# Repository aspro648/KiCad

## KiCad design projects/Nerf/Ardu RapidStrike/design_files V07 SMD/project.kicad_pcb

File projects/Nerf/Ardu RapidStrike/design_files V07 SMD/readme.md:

ArduStrike

Pusher Fuse 1206: 1A https://www.digikey.com/short/p532qq
Main: 1812: 3.5A https://www.digikey.com/short/p532pr

TODO:

ISP to back
second MOSFET?

Main Board
----------------
- 1 ea., IC MCU 8BIT 32KB FLASH 32TQFP, ATMEGA328P-AUR, https://www.digikey.com/short/prrf1p
- 1 ea., Y1 CER RES 16.0000MHZ 15PF SMD, CSTNE16M0V530000R0, https://www.digikey.com/short/p55m1p
- 1 ea., IC REG LINEAR 5V 250MA SOT89-3, Microchip MCP1702-5002E/TO, https://www.digikey.com/short/p5cbrh
- 1 ea., MOSFET N-CH 30V 58A DPAK, Infineon IRLR8729, https://www.digikey.com/short/pm0rdq3
- 1 ea., TC78H611FNG IC MOTOR DRIVER 16TSSOP, https://www.digikey.com/short/p5559f
- 1 ea., PTC RESET FUSE 16V Ih=1.25A It=2.5A  1812, https://www.digikey.com/short/p555q2
- 1 ea., PTC RESET FUSE 16V Ih=500MA It=1A 1210, https://www.digikey.com/short/p532qq
- 1 ea., F1 PTC 1206, Bel 0ZCJ0025AF2E, https://www.digikey.com/short/jfcbc8
- 1 ea., DIODE GEN PURP 50V 1A SMB, https://www.digikey.com/short/p555z5
- 3 ea., Hall Effect Sensor, Diodes Incorporated AH9246-P-B, https://www.digikey.com/short/p5cb4f
- 1 ea., 0.96 Inch 128x64 I2C OLED, https://www.amazon.com/gp/product/B072Q2X2LL/
- 1 ea., CONN HEADER R/A 6POS 2.54MM,  https://www.digikey.com/short/p55hf2

- 7 ea., CAP CER 0.1UF 16V X7R 0805, https://www.digikey.com/short/p5r2hm
- 2 ea., CAP CER 1UF 16V X7R 0805, https://www.digikey.com/short/p5r25m
- 1 ea., CAP CER 10UF 16V X5R 0805, https://www.digikey.com/short/p5r2cv

- 1 ea., RES SMD 100 OHM 5% 1/8W 0805, https://www.digikey.com/short/p55997
- 5 ea., RES SMD 1K OHM 5% 1/8W 0805, https://www.digikey.com/short/p559mn
- 11 ea., RES 10K OHM 1% 1/4W 0805, https://www.digikey.com/short/p55980

- 1 ea., AUDIO PIEZO TRANSDUCER 30V TH, https://www.digikey.com/short/p5r22q

- 1 ea., CONN HEADER R/A 2POS 1.25MM, https://www.digikey.com/short/p5r2dn
- 1 ea., 2POS PicoBlade housing, https://www.digikey.com/short/p4wz0d

- 1 ea., CONN HEADER SMD R/A 3POS https://www.digikey.com/short/p5r208
- 1 ea., 3POS PicoBlade housing, https://www.digikey.com/short/pmwzf2

- 1 ea., CONN HEADER R/A 4POS 1.25MM, https://www.digikey.com/short/p5r2nj
- 1 ea., 4POS PicoBlade housing, https://www.digikey.com/short/p4wzd1

- 1 ea., CONN HEADER SMD R/A 10POS 1.25MM, https://www.digikey.com/short/p5r2vz
- 1 ea., CONN HOUSING 10POS 1.25MM NATURAL, https://www.digikey.com/short/p5rhr3

12" PRE-CRIMP 1853 RED, https://www.digikey.com/short/p4wzvf
12" PRE-CRIMP 1853 BLACK, https://www.digikey.com/short/p4wz1p
12" PRE-CRIMP 1853 BLUE, https://www.digikey.com/short/p4wz14
12" PRE-CRIMP 1853 ORANGE, https://www.digikey.com/short/p4wz1r
12" PRE-CRIMP 1853 GREEN, https://www.digikey.com/short/p4w4c4

10" PRE-CRIMP 1852 RED, https://www.digikey.com/short/p937zh
10" PRE-CRIMP 1852 BLACK, https://www.digikey.com/short/p937zv
10" PRE-CRIMP 1852 YELLOW, https://www.digikey.com/short/p9374t
10" PRE-CRIMP 1852 GREEN, https://www.digikey.com/short/p9374z
10" PRE-CRIMP 1852 ORANGE, https://www.digikey.com/short/p9374f
10" PRE-CRIMP 1852 BLUE, https://www.digikey.com/short/p937mc

16 AWG Silicone wire, https://www.amazon.com/BNTECHGO-Silicone-Flexible-Strands-Stranded/dp/B00TG1TRL2
18 AWG Silicone wire (7.5A, $0.40/ft), https://www.amazon.com/Silicone-Electrical-Conductor-Parallel-Flexible/dp/B07FMRDP87
16 AWG Silicone wire (12A, $0.70/ft), https://www.amazon.com/Silicone-Electrical-Conductor-Parallel-Flexible/dp/B07FMLVF84

XT60 connector male

Optional:
FTDI SERIAL TTL-232 USB CABLE, https://www.digikey.com/short/p4w47d
SPARKFUN FT231X BREAKOUT, https://www.digikey.com/short/p4w4qb
- 1 ea., 3mm IR LED, https://www.digikey.com/short/pmwzdq
- 1 ea., NPN photo transistor, https://www.digikey.com/short/pmwzdb

Motor Spec Sheet:
----------------
https://docs.google.com/spreadsheets/d/12gOU-GbuqdGVzpOjZJvQ_gq1Nmw63c_sd13Wt4bfn1E/edit#gid=0

Revisions
----------------
0.1 Added push button to A0.
0.3 Removed XT30 connectors, added PTC, fuse holder.
0.4 Major component repositioning
0.5 Trigger moved clip connector
	Pusher Bat conn to 5.08mm.
	Mosfet layout change
0.6 SMD Layout
0.7 Picoblade, piezo, FTDI to through-hole. 10K resistor divider.

License
----------------
[Attribution-ShareAlike 3.0 United States (CC BY-SA 3.0 US)](https://creativecommons.org/licenses/by-sa/3.0/us/)

You are free to:

- Share — copy and redistribute the material in any medium or format
- Adapt — remix, transform, and build upon the material

Under the following terms:

- Attribution — You must give appropriate credit, provide a link to the license, and indicate if changes were made. You may do so in any reasonable manner, but not in any way that suggests the licensor endorses you or your use.
- ShareAlike — If you remix, transform, or build upon the material, you must distribute your contributions under the same license as the original.

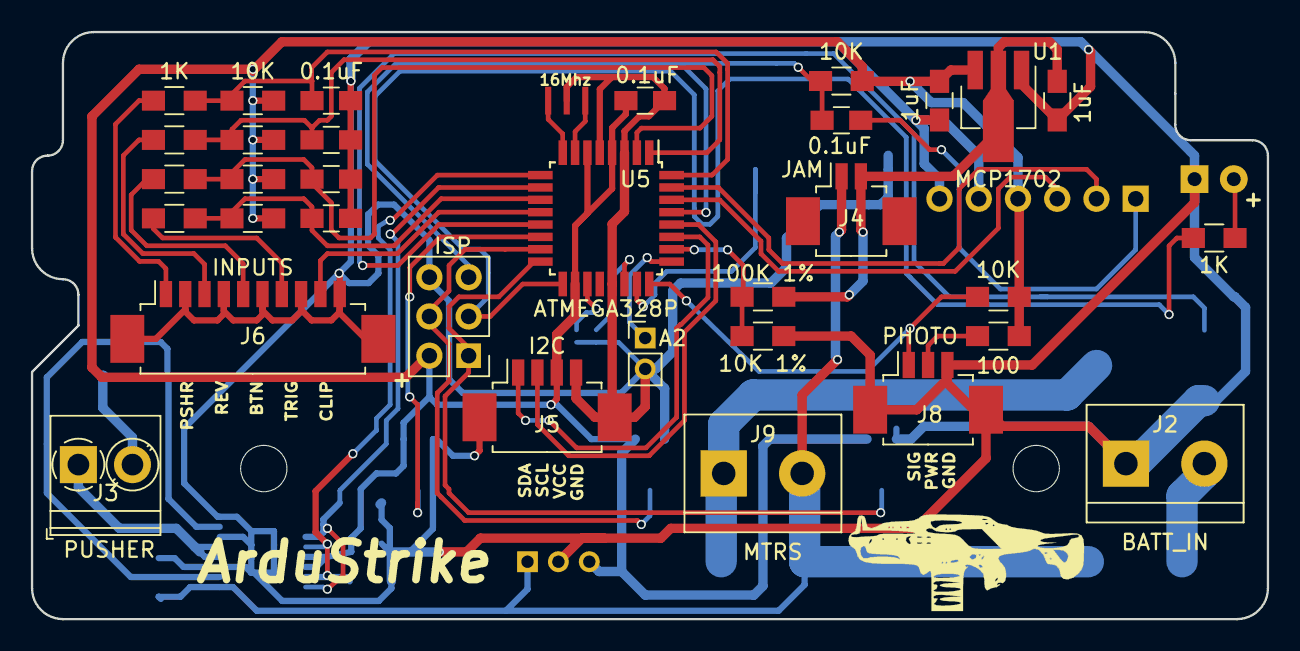
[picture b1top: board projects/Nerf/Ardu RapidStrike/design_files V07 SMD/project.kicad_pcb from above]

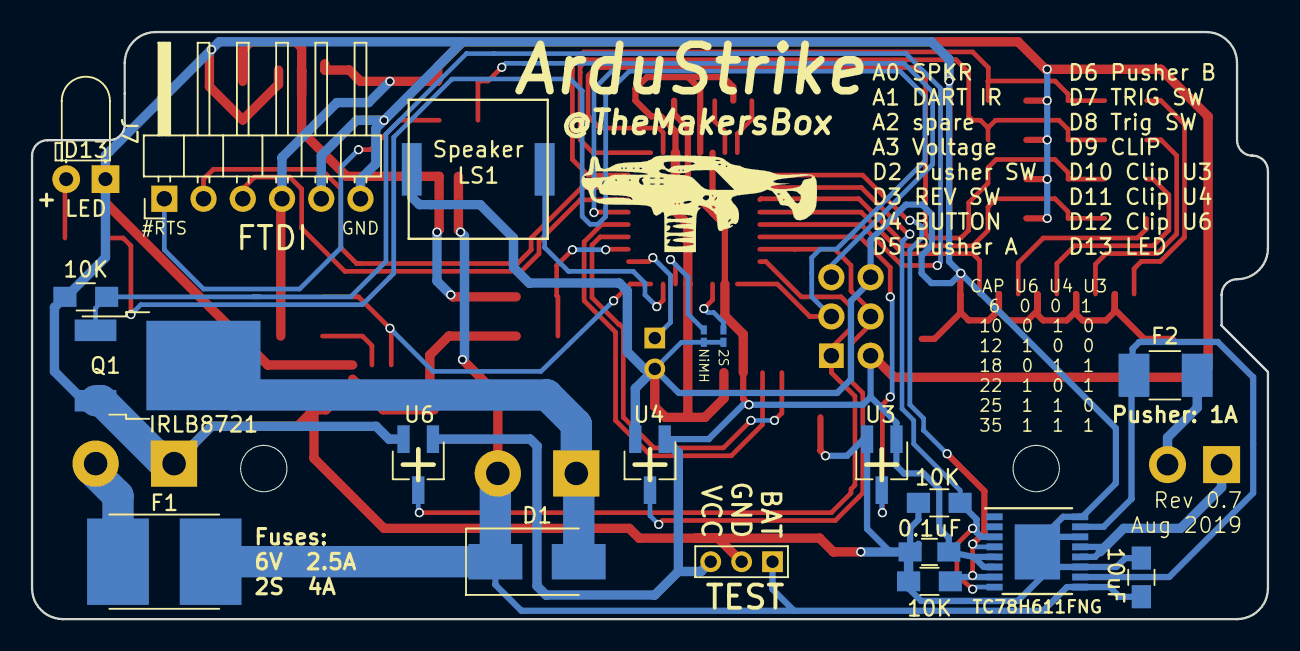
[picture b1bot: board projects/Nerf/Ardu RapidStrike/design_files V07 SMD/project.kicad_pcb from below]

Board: 2 copper layers, 80.0 x 38.0 mm, 55 parts (19 on the bottom side), 41 nets.

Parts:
C1, C4: 1uF; C_0805_HandSoldering
C2: 10uF; C_0805_HandSoldering
C3, C5, C6, C7, C8, C9, C10: 0.1uF; C_0805_HandSoldering
CON1: ISP; Pin_Header_Straight_2x03_Pitch2.54mm
D1: KICKBACK; D_SMB_Handsoldering
D13: LED; LED_D3.0mm_Horizontal_O1.27mm_Z10.0mm
F1: PTC; Fuse_SMD2920
F2: PTC; Fuse_SMD1210
J1: TEST; Pin_Header_Straight_1x03_Pitch2.00mm
J2: BATT_IN; TerminalBlock_bornier-2_P5.08mm
J3: PUSHER; TerminalBlock_Phoenix_PT-1,5-2-3.5-H_1x02_P3.50mm_Horizontal
J4: JAM; Molex_PicoBlade_53261-0271_02x1.25mm_Angled
J5: I2C; Molex_PicoBlade_53261-0471_04x1.25mm_Angled
J6: INPUTS; Molex_PicoBlade_53261-1071_10x1.25mm_Angled
J7: FTDI; Pin_Header_Angled_1x06_Pitch2.54mm
J8: PHOTO; Molex_PicoBlade_53261-0371_03x1.25mm_Angled
J9: MTRS; TerminalBlock_bornier-2_P5.08mm
J11: A2; Pin_Header_Straight_1x02_Pitch2.00mm
J14, J14#2: NPTH; SolderWirePad_single_2-5mmDrill
JP1: 2S; JMPR
JP2: NiMH; JMPR
LS1: Speaker; PS1240_piezo
Q1: IRLB8721; TO-252-2_hand_soldering
R1, R3, R4, R6, R9, R10, R17, R19, R20: 10K; R_0805_HandSoldering
R2, R5, R7, R11, R18: 1K; R_0805_HandSoldering
R8: 100K 1%; R_0805_HandSoldering
R12: 10K 1%; R_0805_HandSoldering
R21: 100; R_0805_HandSoldering
U1: MCP1702; SOT-89-3_Handsoldering
U2: TC78H611FNG; TSSOP-16-1EP_4.4x5mm_Pitch0.65mm
U3, U4, U6: HALL SENSOR; SC-59_Handsoldering
U5: ATMEGA328P; TQFP-32_7x7mm_Pitch0.8mm
Y1: 16Mhz; Resonator_SMD_CTSC_1.3mmx3.2mm

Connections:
/0(Rx): J7.3, U5.30
/1(Tx): J7.2, U5.31
/2: C6.1, R4.1, R5.2, U5.32
/3(**): C7.1, R6.1, R7.2, U5.1
/4: C10.1, R18.2, R19.1, U5.2
/5(**): R1.2, U2.4, U2.7, U5.9
/6(**): R3.2, U2.3, U2.8, U5.10
/7: C8.1, R10.1, R11.2, U5.11
/8: J6.9, U5.12
/9(**): Q1.1, R9.2, U5.13
/10(SS): U3.3, U5.14
/11(MOSI): CON1.4, U4.3, U5.15
/12(MISO): CON1.1, U5.16, U6.3
/13(SCK): CON1.3, R2.1, U5.17
/#RTS: C9.1, J7.1
/A0: LS1.1, U5.23
/A1: J8.1, R20.2, U5.24
/A2: J11.1, U5.25
/A3: R8.1, R12.1, U5.26
/A4(SDA): J5.1, U5.27
/A5(SCL): J5.2, U5.28
/BATT: C2.1, D1.1, F1.1, J1.1, J4.1, J9.2, U2.9
/Reset: C9.2, CON1.5, R17.1, U5.29
/Vin: C1.1, J4.2, R8.2, U1.2
GND: C1.2, C2.2, C3.2, C4.2, C5.2, C6.2, C7.2, C8.2, C10.2, CON1.6, D13.1, J1.2, J2.1, J5.4, J6.2, J6.4, J6.6, J6.8, J6.10, J7.5, J7.6, J8.3, J11.2, JP1.1, JP2.1, LS1.2, Q1.3, R1.1, R3.1, R9.1, R12.2, U1.1, U2.11, U2.14, U2.16, U3.2, U4.2, U5.3, U5.5, U5.21, U6.2, Y1.2
unnamed: D1.2, J9.1, Q1.2
unnamed: D13.2, R2.2
unnamed: F1.2, J2.2
unnamed: F2.1, U2.10, U2.15
unnamed: F2.2, J3.2
unnamed: J3.1, U2.12, U2.13
unnamed: J6.1, R5.1
unnamed: J6.3, R7.1
unnamed: J6.5, R18.1
unnamed: J6.7, R11.1
unnamed: J8.2, R21.2
unnamed: JP1.2, U5.19
unnamed: JP2.2, U5.22
unnamed: U5.7, Y1.3
unnamed: U5.8, Y1.1
VCC: C3.1, C4.1, C5.1, CON1.2, J1.3, J5.3, J7.4, R4.2, R6.2, R10.2, R17.2, R19.2, R20.1, R21.1, U1.3, U2.5, U2.6, U3.1, U4.1, U5.4, U5.6, U5.18, U6.1

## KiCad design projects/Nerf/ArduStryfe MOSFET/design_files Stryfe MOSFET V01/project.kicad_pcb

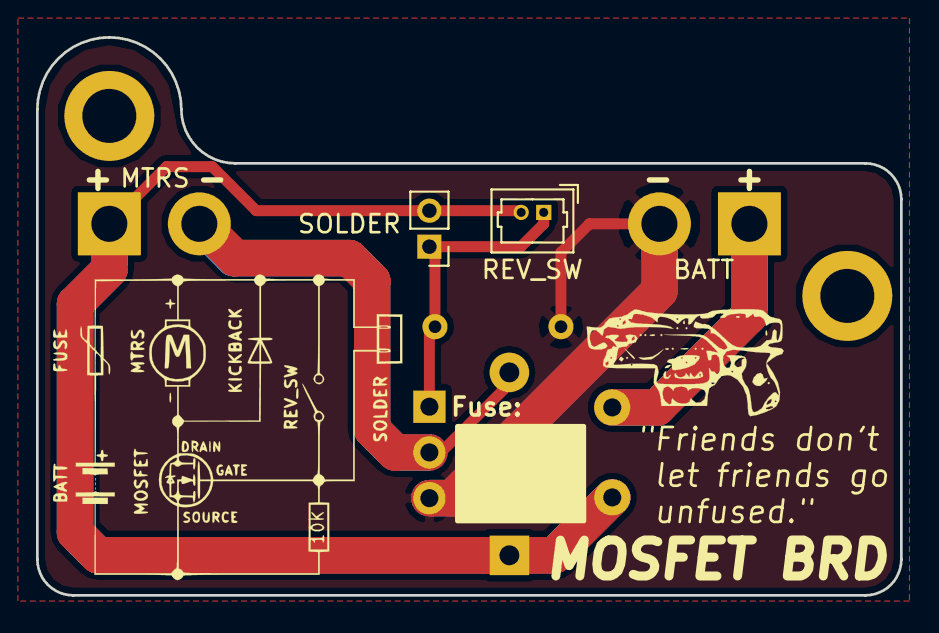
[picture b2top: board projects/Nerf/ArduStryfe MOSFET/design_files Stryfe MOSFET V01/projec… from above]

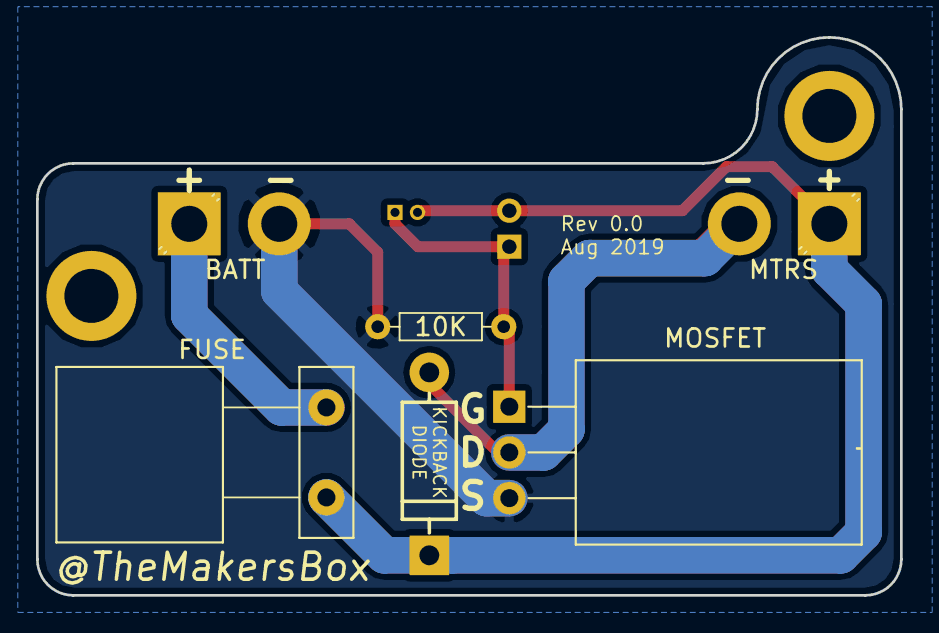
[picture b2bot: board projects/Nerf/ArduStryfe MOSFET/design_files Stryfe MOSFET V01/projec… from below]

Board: 2 copper layers, 48.0 x 31.0 mm, 11 parts (6 on the bottom side), 5 nets.

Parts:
BT1: BATT; Terminal_no_silk
D1: KICKBACK; D_DO-41
F1: FUSE; Fuse_Littelfuse-LVR125
J1: REV_SW; Molex_PicoBlade_53047-0210_02x1.25mm_Straight
J3: SOLDER; Pin_Header_Straight_1x02_Pitch2.00mm
J14, J14#2: MOUNT; SolderWirePad_single_2-5mmDrill
M1: MTRS; Terminal_no_silk
Q1: MOSFET; TO-220-3_Horizontal
R1: 10K; R__P7mm
Ref**: Val**; sch

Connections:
GND: BT1.2, Q1.3, R1.1
unnamed: BT1.1, F1.2
unnamed: D1.1, F1.1, J1.2, J3.2, M1.1
unnamed: D1.2, M1.2, Q1.2
unnamed: J1.1, J3.1, Q1.1, R1.2

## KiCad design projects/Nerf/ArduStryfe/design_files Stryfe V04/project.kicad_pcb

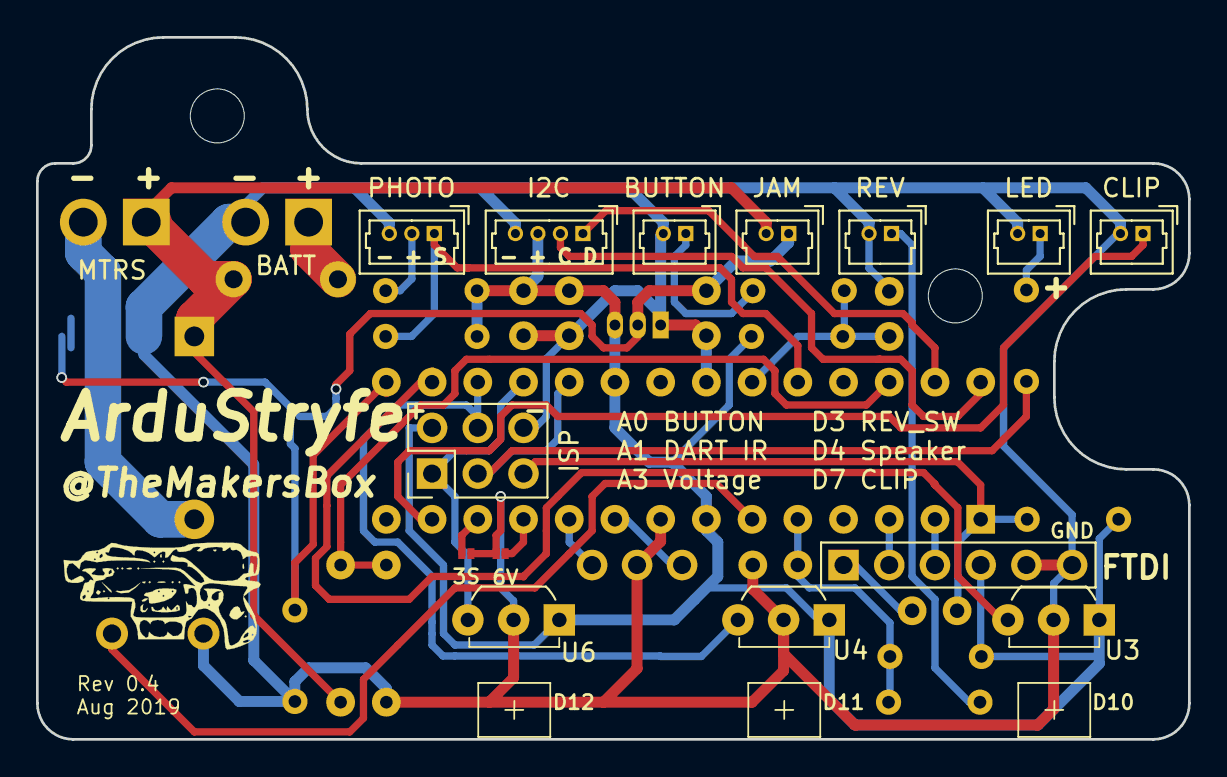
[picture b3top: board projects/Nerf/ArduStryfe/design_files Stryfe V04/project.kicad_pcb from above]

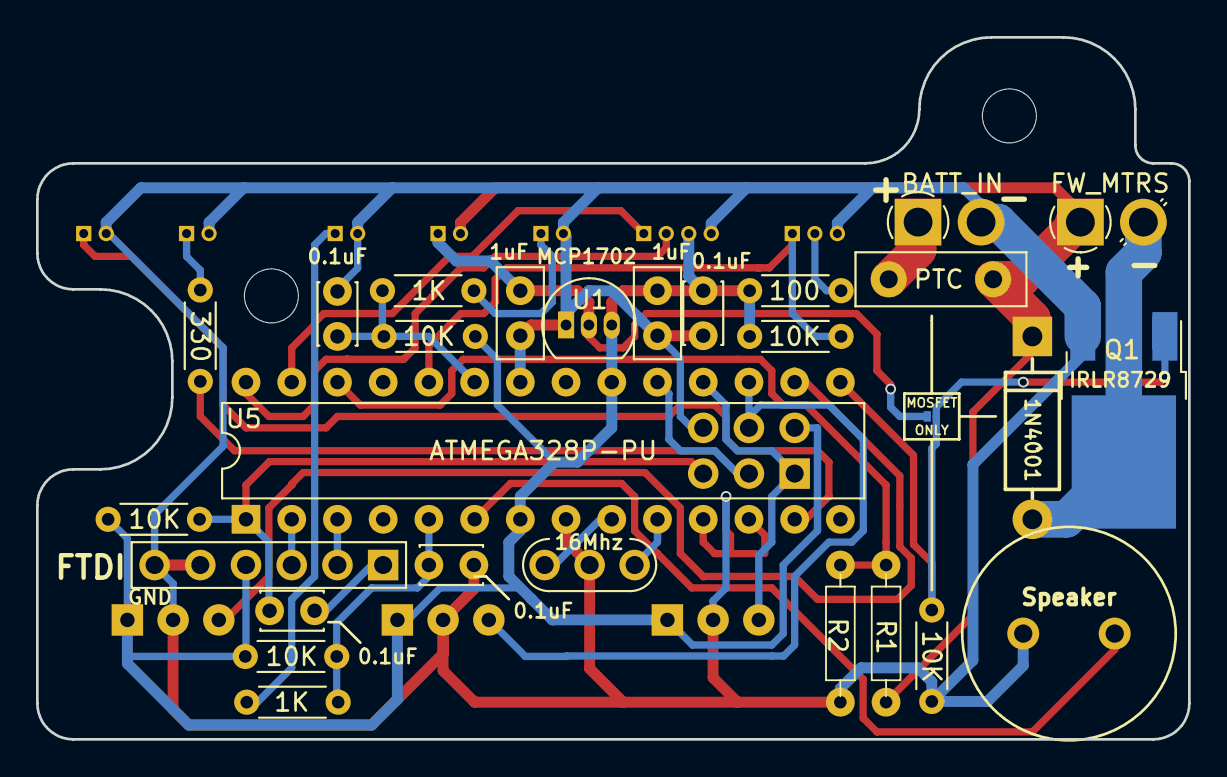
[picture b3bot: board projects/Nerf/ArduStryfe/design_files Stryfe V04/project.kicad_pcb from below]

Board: 2 copper layers, 64.0 x 39.0 mm, 43 parts (28 on the bottom side), 31 nets.

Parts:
C1, C4: 1uF; C_Disc_D5.0mm_W2.5mm_P2.50mm
C5, C7, C9, C10: 0.1uF; C_Disc_D3.4mm_W2.1mm_P2.50mm
CON1: ISP; Pin_Header_Straight_2x03_Pitch2.54mm
D1: 1N4001; D_DO-41
F1: PTC; Fuse_Littelfuse-LVR125
J1: JAM; Molex_PicoBlade_53047-0210_02x1.25mm_Straight
J2: BATT_IN; TerminalBlock_P3.50mm_Horizontal
J3: LED; Molex_PicoBlade_53047-0210_02x1.25mm_Straight
J5: I2C; Molex_PicoBlade_53047-0410_04x1.25mm_Straight
J6: REV; Molex_PicoBlade_53047-0210_02x1.25mm_Straight
J7: FTDI; Pin_Header_Straight_1x06_Pitch2.54mm
J8: PHOTO; Molex_PicoBlade_53047-0310_03x1.25mm_Straight
J9: FW_MTRS; TerminalBlock_P3.50mm_Horizontal
J12: CLIP; Molex_PicoBlade_53047-0210_02x1.25mm_Straight
J14, J14#2: NPTH; SolderWirePad_single_2-5mmDrill
J21: BUTTON; Molex_PicoBlade_53047-0210_02x1.25mm_Straight
JP1: 6V; JMP
JP2: 3S; JMP
JP3: MOSFET_ONLY; JMP
LS1: Speaker; SPEAKER
Q1: IRLR8729; TO-252-2_hand_soldering
R1, R2: 10K 1%; R_7.5mm
R6, R9, R17, R19, R20: 10K; R__P5.08mm
R7, R18: 1K; R__P5.08mm
R12: 330; R__P5.08mm
R21: 100; R__P5.08mm
U1: MCP1702; TO-92_Inline_Narrow_Oval
U3, U4, U6: HALL SENSOR; Hall_Sensor
U5: ATMEGA328P-PU; DIP-28_W7.62mm
Y1: 16Mhz; Resonator-3pin_w7.0mm_h2.5mm

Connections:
/0(Rx): J7.3, U5.2
/1(Tx): J7.2, U5.3
/3(**): C7.1, R6.1, R7.2, U5.5
/4: LS1.1, U5.6
/5(**): JP1.1, U5.11
/6(**): JP2.1, U5.12
/7: J12.1, U5.13
/9(**): JP3.2, Q1.1, R9.2, U5.15
/10(SS): U3.3, U5.16
/11(MOSI): CON1.4, U4.3, U5.17
/12(MISO): CON1.1, U5.18, U6.3
/13(SCK): CON1.3, R12.1, U5.19
/#RTS: C9.1, J7.1
/A0: C10.1, R18.2, R19.1, U5.23
/A1: J8.1, R20.2, U5.24
/A3: R1.1, R2.1, U5.26
/A4(SDA): J5.1, U5.27
/A5(SCL): J5.2, U5.28
/BATT: D1.1, F1.1, J1.2, J9.1, R1.2
/Reset: C9.2, CON1.5, R17.1, U5.1
GND: C1.2, C4.2, C5.2, C7.2, C10.2, CON1.6, J2.2, J3.2, J5.4, J6.2, J7.5, J7.6, J8.3, J12.2, J21.2, JP1.2, JP2.2, LS1.2, Q1.3, R2.2, R9.1, U1.1, U3.2, U4.2, U5.8, U5.22, U6.2, Y1.2
unnamed: C1.1, J1.1, JP3.1, U1.2
unnamed: D1.2, J9.2, Q1.2
unnamed: F1.2, J2.1
unnamed: J3.1, R12.2
unnamed: J6.1, R7.1
unnamed: J8.2, R21.2
unnamed: J21.1, R18.1
unnamed: U5.9, Y1.3
unnamed: U5.10, Y1.1
VCC: C4.1, C5.1, CON1.2, J5.3, J7.4, R6.2, R17.2, R19.2, R20.1, R21.1, U1.3, U3.1, U4.1, U5.7, U5.20, U6.1

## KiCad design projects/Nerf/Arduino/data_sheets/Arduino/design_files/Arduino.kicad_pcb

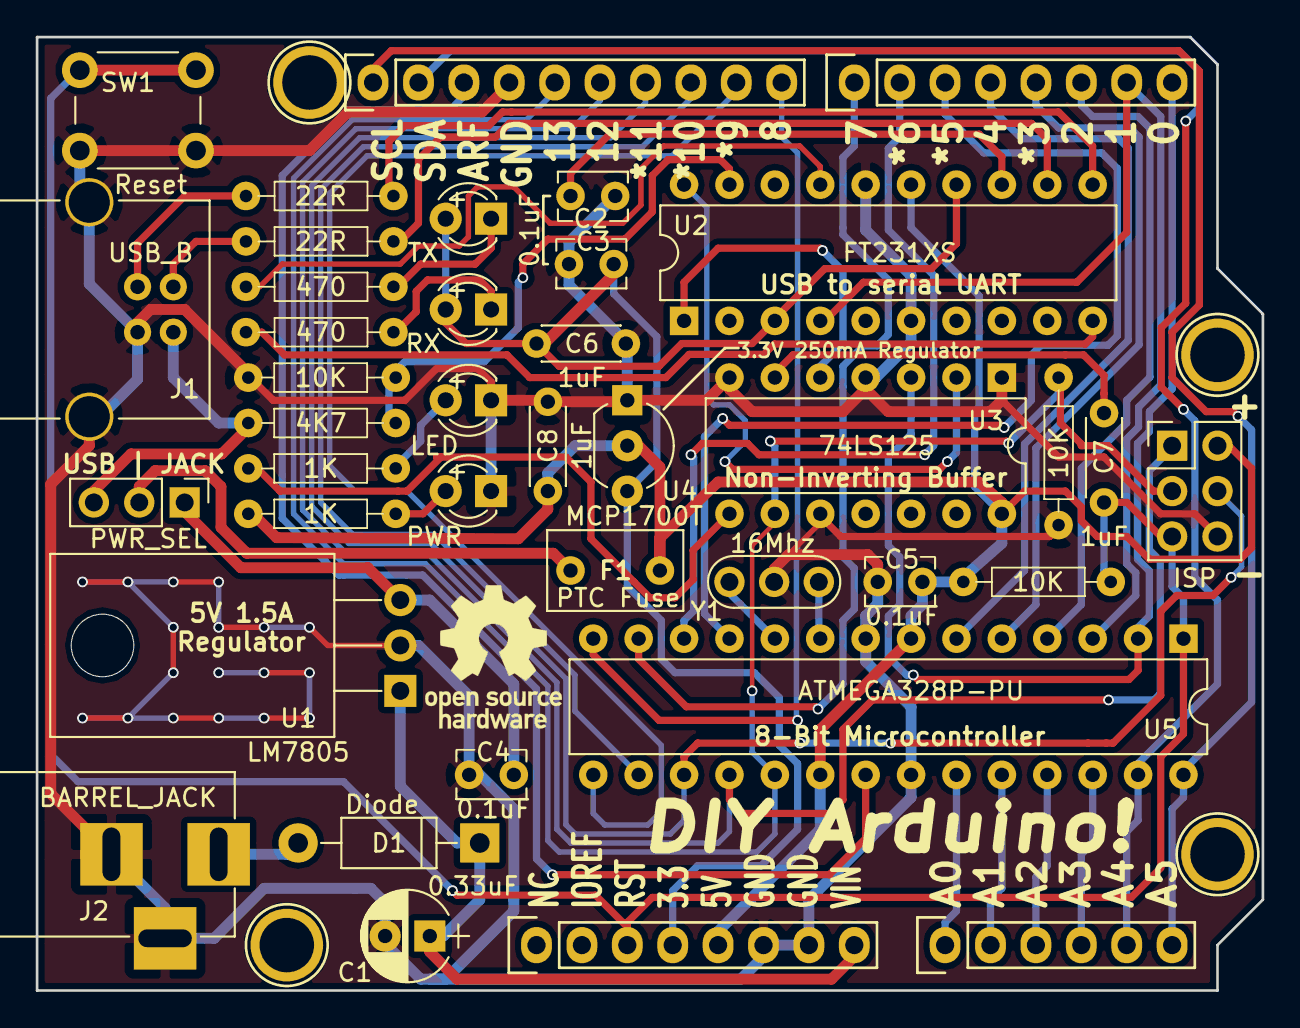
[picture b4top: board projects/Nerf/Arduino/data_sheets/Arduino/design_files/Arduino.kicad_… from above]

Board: 2 copper layers, 68.6 x 53.3 mm, 43 parts (0 on the bottom side), 48 nets.

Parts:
C1: 0.33uF; CP_Radial_D5.0mm_P2.50mm
C2, C3, C4, C5: 0.1uF; C_Disc_D3.8mm_W2.6mm_P2.50mm
C6, C7, C8: 1uF; C_Disc_D4.3mm_W1.9mm_P5.00mm
CON1: ISP; Pin_Header_Straight_2x03_Pitch2.54mm
D1: Schottky; D_DO-41_SOD81_P10.16mm_Horizontal
D2: PWR; LED_D3.0mm
D3: TX; LED_D3.0mm
D4: RX; LED_D3.0mm
D13: LED; LED_D3.0mm
F1: PTC Fuse; C_Disc_D7.5mm_W4.4mm_P5.00mm
J1: USB_B
J2: BARREL_JACK
J3: PWR_SEL; Pin_Header_Straight_1x03_Pitch2.54mm
P1: Power; Socket_Strip_Arduino_1x08
P2: Analog; Socket_Strip_Arduino_1x06
P3: Digital; Socket_Strip_Arduino_1x10
P4: Digital; Socket_Strip_Arduino_1x08
P5, P6, P7, P8: CONN_01X01; Arduino_1pin
R1: 4K7; R_Axial_DIN0204_L3.6mm_D1.6mm_P7.62mm_Horizontal
R2, R13: 1K; R_Axial_DIN0204_L3.6mm_D1.6mm_P7.62mm_Horizontal
R3, R4: 470; R_Axial_DIN0204_L3.6mm_D1.6mm_P7.62mm_Horizontal
R5, R6: 22R; R_Axial_DIN0204_L3.6mm_D1.6mm_P7.62mm_Horizontal
R7, R8, R9: 10K; R_Axial_DIN0204_L3.6mm_D1.6mm_P7.62mm_Horizontal
SW1: Reset; SW_PUSH_6mm
U1: LM7805; TO-220-3_Horizontal
U2: FT231XS; DIP-20_W7.62mm
U3: 74LS125; DIP-14_W7.62mm
U4: MCP1700T; TO-92_Inline_Wide
U5: ATMEGA328P-PU; DIP-28_W7.62mm
Y1: 16Mhz; Resonator-3pin_w7.0mm_h2.5mm

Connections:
+3V3: C3.1, C6.1, D3.2, D4.2, P1.4, U2.3, U2.14, U4.2
/0(RX): P4.8, U3.3, U5.2
/1(TX): P4.7, U2.4, U5.3
/2: P4.6, U5.4
/3(**): P4.5, U5.5
/4: P4.4, U5.6
/5(**): P4.3, U5.11
/6(**): P4.2, U5.12
/7: P4.1, U5.13
/8: P3.10, U5.14
/9(**): P3.9, U5.15
/10(SS): P3.8, U5.16
/11(MOSI): CON1.4, P3.7, U5.17
/12(MISO): CON1.1, P3.6, U5.18
/13(SCK): CON1.3, P3.5, R9.2, U3.9, U5.19
/A0: P2.1, U5.23
/A1: P2.2, U5.24
/A2: P2.3, U5.25
/A3: P2.4, U5.26
/A4(SDA): P2.5, P3.2, U5.27
/A5(SCL): P2.6, P3.1, U5.28
/AREF: P3.3, U5.21
/D+: J1.3, R5.2
/D-: J1.2, R6.2
/Reset: C7.1, CON1.5, P1.3, R8.1, SW1.2, U5.1
/USBVCC: J1.1, J3.3, R1.1
/Vin: C1.1, D1.1, P1.8, U1.1
GND: C1.2, C2.2, C3.2, C4.2, C5.2, C6.2, C8.2, CON1.6, D2.1, D13.1, J1.4, J1.5, J2.2, J2.3, P1.6, P1.7, P3.4, R7.1, R9.1, SW1.1, U1.2, U2.6, U2.16, U3.1, U3.4, U3.7, U3.10, U4.1, U5.8, U5.22, Y1.2
unnamed: C2.1, U2.13
unnamed: C4.1, J3.1, U1.3
unnamed: C7.2, U3.6
unnamed: D1.2, J2.1
unnamed: D2.2, R2.2
unnamed: D3.1, R3.1
unnamed: D4.1, R4.1
unnamed: D13.2, R13.2
unnamed: F1.1, J3.2
unnamed: R1.2, R7.2, U2.19
unnamed: R3.2, U2.17
unnamed: R4.2, U2.10
unnamed: R5.1, U2.11
unnamed: R6.1, U2.12
unnamed: R13.1, U3.8
unnamed: U2.1, U3.5
unnamed: U2.20, U3.2
unnamed: U5.9, Y1.3
unnamed: U5.10, Y1.1
VCC: C5.1, C8.1, CON1.2, F1.2, P1.5, R2.1, R8.2, U2.15, U3.14, U4.3, U5.7, U5.20

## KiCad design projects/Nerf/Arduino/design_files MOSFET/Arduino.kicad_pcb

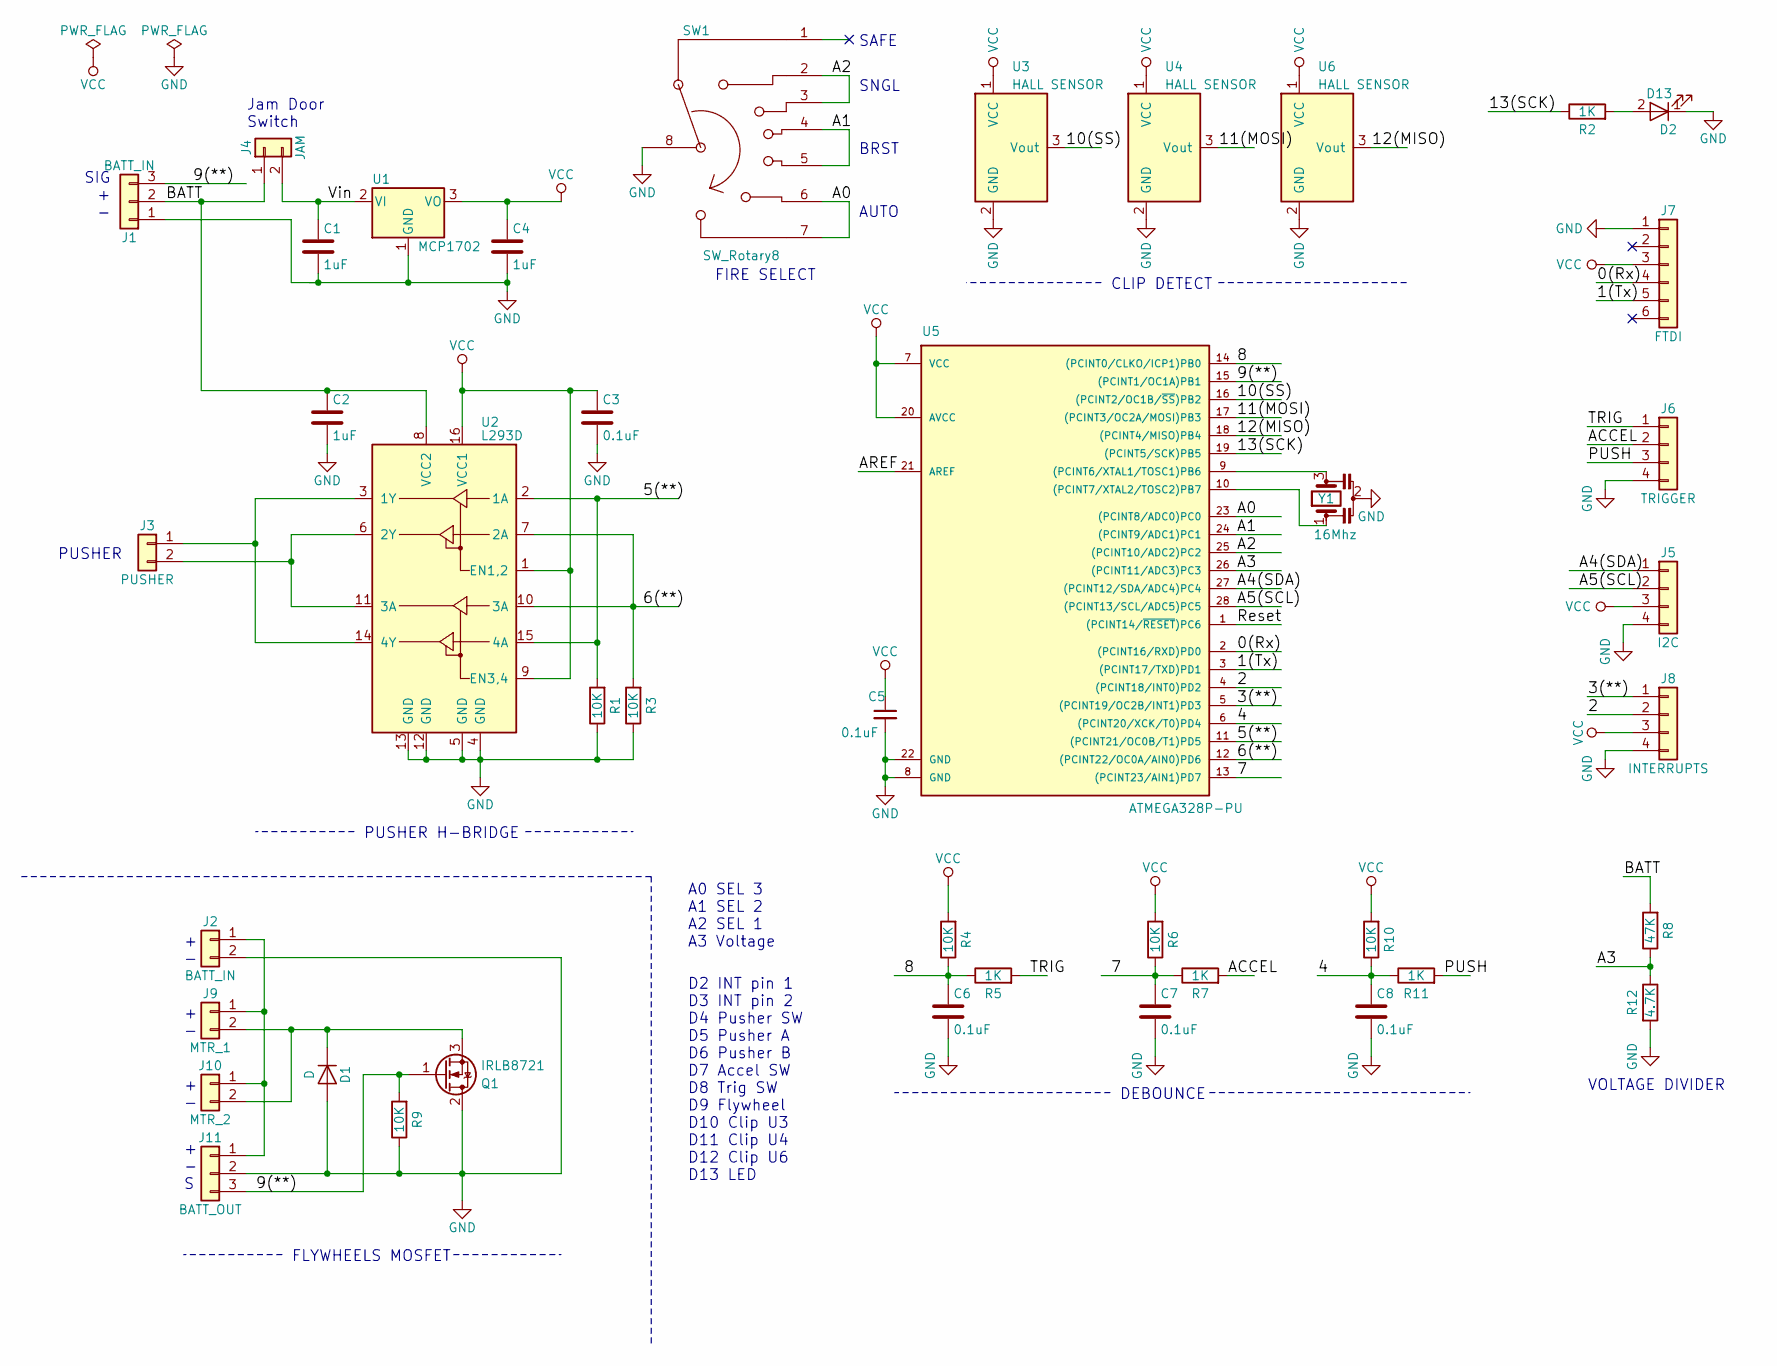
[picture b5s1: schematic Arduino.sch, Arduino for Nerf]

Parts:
C1, C2, C4: 1uF; C_Disc_D5.0mm_W2.5mm_P2.50mm
C3, C6, C7, C8: 0.1uF; C_Disc_D3.4mm_W2.1mm_P2.50mm
C5: 0.1uF; C_Disc_D3.8mm_W2.6mm_P2.50mm
D1: D; D_DO-15_P12.70mm_Horizontal
D2: D13; LED_D3.0mm_Horizontal_O1.27mm_Z10.0mm
J1: BATT_IN; PhoenixContact_MCV-G_03x3.50mm_Vertical
J2: BATT_IN; PhoenixContact_GMSTBVA-G_02x7.50mm_Vertical
J3: PUSHER; PhoenixContact_MCV-G_02x3.50mm_Vertical
J4: JAM; PhoenixContact_MCV-G_02x3.50mm_Vertical
J5: I2C; Pin_Header_Straight_1x04_Pitch2.54mm
J6: TRIGGER; Pin_Header_Straight_1x04_Pitch2.54mm
J7: FTDI; Pin_Header_Straight_1x06_Pitch2.54mm
J8: INTERRUPTS; Pin_Header_Straight_1x04_Pitch2.54mm
J9: MTR_1; PhoenixContact_GMSTBVA-G_02x7.50mm_Vertical
J10: MTR_2; PhoenixContact_GMSTBVA-G_02x7.50mm_Vertical
J11: BATT_OUT; PhoenixContact_MCV-G_03x3.50mm_Vertical
Q1: IRLB8721; TO-220-3_Horizontal
R1, R3, R4, R6, R9, R10: 10K; R_Axial_DIN0204_L3.6mm_D1.6mm_P7.62mm_Horizontal
R2, R5, R7, R11: 1K; R_Axial_DIN0204_L3.6mm_D1.6mm_P7.62mm_Horizontal
R8: 47K; R_Axial_DIN0204_L3.6mm_D1.6mm_P7.62mm_Horizontal
R12: 4.7K; R_Axial_DIN0204_L3.6mm_D1.6mm_P7.62mm_Horizontal
SW1: SW_Rotary8; Pin_Header_Straight_1x08_Pitch2.54mm
U1: MCP1702; TO-92_Inline_Narrow_Oval
U2: L293D; DIP-16_W7.62mm
U3, U4, U6: HALL SENSOR; TO-92_Inline_Wide
U5: ATMEGA328P-PU; DIP-28_W7.62mm
Y1: 16Mhz; Resonator-3pin_w7.0mm_h2.5mm

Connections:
/0(Rx): J7.4, U5.2 ((PCINT16/RXD)PD0)
/1(Tx): J7.5, U5.3 ((PCINT17/TXD)PD1)
/2: J8.2, U5.4 ((PCINT18/INT0)PD2)
/3(**): J8.1, U5.5 ((PCINT19/OC2B/INT1)PD3)
/4: C8.1, R10.1, R11.1, U5.6 ((PCINT20/XCK/T0)PD4)
/5(**): R1.2, U2.2 (1A), U2.15 (4A), U5.11 ((PCINT21/OC0B/T1)PD5)
/6(**): R3.2, U2.7 (2A), U2.10 (3A), U5.12 ((PCINT22/OC0A/AIN0)PD6)
/7: C7.1, R6.1, R7.1, U5.13 ((PCINT23/AIN1)PD7)
/8: C6.1, R4.1, R5.1, U5.14 ((PCINT0/CLKO/ICP1)PB0)
/9(**): J1.3, J11.3, Q1.1 (G), R9.2, U5.15 ((PCINT1/OC1A)PB1)
/10(SS): U3.3 (Vout), U5.16 ((PCINT2/OC1B/~SS~)PB2)
/11(MOSI): U4.3 (Vout), U5.17 ((PCINT3/OC2A/MOSI)PB3)
/12(MISO): U5.18 ((PCINT4/MISO)PB4), U6.3 (Vout)
/13(SCK): R2.1, U5.19 ((PCINT5/SCK)PB5)
/A0: SW1.6, SW1.7, U5.23 ((PCINT8/ADC0)PC0)
/A1: SW1.4, SW1.5, U5.24 ((PCINT9/ADC1)PC1)
/A2: SW1.2, SW1.3, U5.25 ((PCINT10/ADC2)PC2)
/A3: R8.1, R12.1, U5.26 ((PCINT11/ADC3)PC3)
/A4(SDA): J5.1, U5.27 ((PCINT12/SDA/ADC4)PC4)
/A5(SCL): J5.2, U5.28 ((PCINT13/SCL/ADC5)PC5)
/ACCEL: J6.2, R7.2
/AREF: U5.21 (AREF)
/BATT: C2.1, J1.2, J4.1, R8.2, U2.8 (VCC2)
/PUSH: J6.3, R11.2
/Reset: U5.1 ((PCINT14/~RESET~)PC6)
/TRIG: J6.1, R5.2
/Vin: C1.1, J4.2, U1.2 (VI)
GND: C1.2, C2.2, C3.2, C4.2, C5.2, C6.2, C7.2, C8.2, D1.2 (A), D2.1 (K), J1.1, J2.2, J5.4, J6.4, J7.1, J8.4, J11.2, Q1.2 (D), R1.1, R3.1, R9.1, R12.2, SW1.8, U1.1 (GND), U2.4 (GND), U2.5 (GND), U2.12 (GND), U2.13 (GND), U3.2 (GND), U4.2 (GND), U5.8 (GND), U5.22 (GND), U6.2 (GND), Y1.2
unnamed: D1.1 (K), J9.2, J10.2, Q1.3 (S)
unnamed: D2.2 (A), R2.2
unnamed: J3.1, U2.3 (1Y), U2.14 (4Y)
unnamed: J3.2, U2.6 (2Y), U2.11 (3A)
unnamed: J2.1, J9.1, J10.1, J11.1
unnamed: U5.9 ((PCINT6/XTAL1/TOSC1)PB6), Y1.3
unnamed: U5.10 ((PCINT7/XTAL2/TOSC2)PB7), Y1.1
VCC: C3.1, C4.1, C5.1, J5.3, J7.3, J8.3, R4.2, R6.2, R10.2, U1.3 (VO), U2.1 (EN1,2), U2.9 (EN3,4), U2.16 (VCC1), U3.1 (VCC), U4.1 (VCC), U5.7 (VCC), U5.20 (AVCC), U6.1 (VCC)

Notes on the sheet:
SIG + -
PUSHER
Jam Door Switch
DEBOUNCE
VOLTAGE DIVIDER
FIRE SELECT
CLIP DETECT
PUSHER H-BRIDGE
FLYWHEELS MOSFET
+ -
+ - S
SAFE
SNGL
BRST
AUTO
D2 INT pin 1 D3 INT pin 2 D4 Pusher SW D5 Pusher A D6 Pusher B D7 Accel SW D8 Trig SW D9 Flywheel D10 Clip U3 D11 Clip U4 D12 Clip U6 D13 LED
A0 SEL 3 A1 SEL 2 A2 SEL 1 A3 Voltage

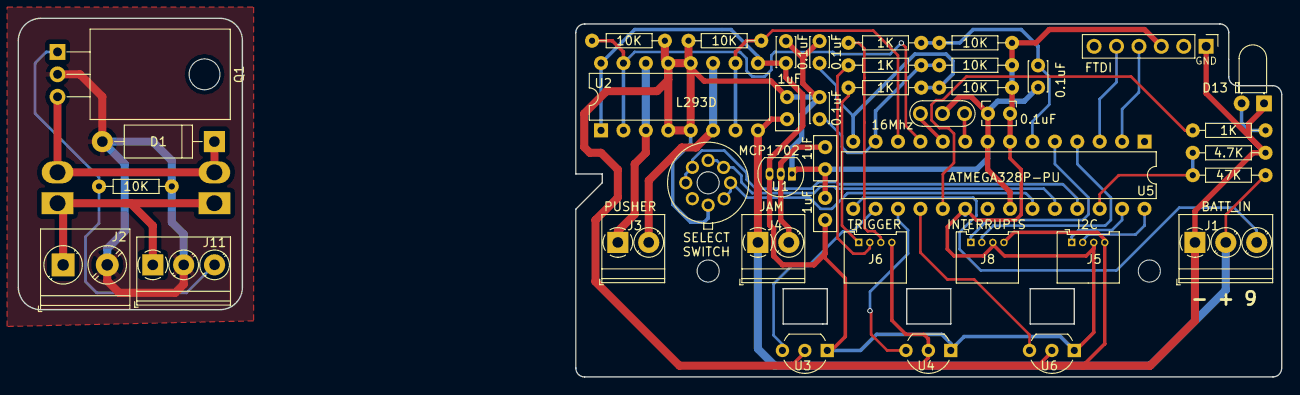
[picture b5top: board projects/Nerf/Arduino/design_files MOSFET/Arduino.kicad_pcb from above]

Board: 2 copper layers, 80.0 x 40.0 mm, 42 parts (0 on the bottom side), 34 nets.
